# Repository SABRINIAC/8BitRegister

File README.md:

# CPU Registers & Tristate Buffers for the SABRINIAC
This project creates the PCBs for my CPU registers and the tristate buffers to I/O with them.

It is for my '60s inspired computer im making base don the Intel 8080. At the time of writing this I have RAM + it's clock done and the ALU Modules done. After I get the registers + buffers I'll only have to make a motherboard and an opcode decoder/microcode.

The SABRINIAC is my '60s inspired, transistor based,, Intel 8008 Architecture computer. Every part of it from the instruction decoder to the alu will be built using purely transistors.

You can check out the other repos for the SABRINAIC's parts [here](https://github.com/orgs/SABRINIAC/repositories) or you can check out the ALU's repo which explains in more detail what the SABRINIAC is [here](https://github.com/SABRINIAC/ALU-Components)

How to assemble? Just solder on all of the 2N2222 Transistors (or other NPN transitors) and 0603 1kohm resistors

BOM:

| Part Name | Count | Link | Cost |
|-----------|-------|------|------|
| Register PCBs | 18 | From JLCPCB | $10.20 |
| Tri-State Buffer PCBs | 26 | From JLCPCB | $13.30 |
| 2N2222 NPN Transistors | 1406 | https://www.aliexpress.us/item/3256806831821651.html | $15 |
| 0603 SMD 1kohm Resistors | 2684 | https://www.aliexpress.us/item/3256805937811409.html | $12.56 |
| Pin headers | Any combination of 1xN Right Angle Male Pin Headers to make up 1x854 | I already have them but something like this: https://www.aliexpress.us/item/3256803319359683.html | $3 |
| Total | - | - | ~$70 |

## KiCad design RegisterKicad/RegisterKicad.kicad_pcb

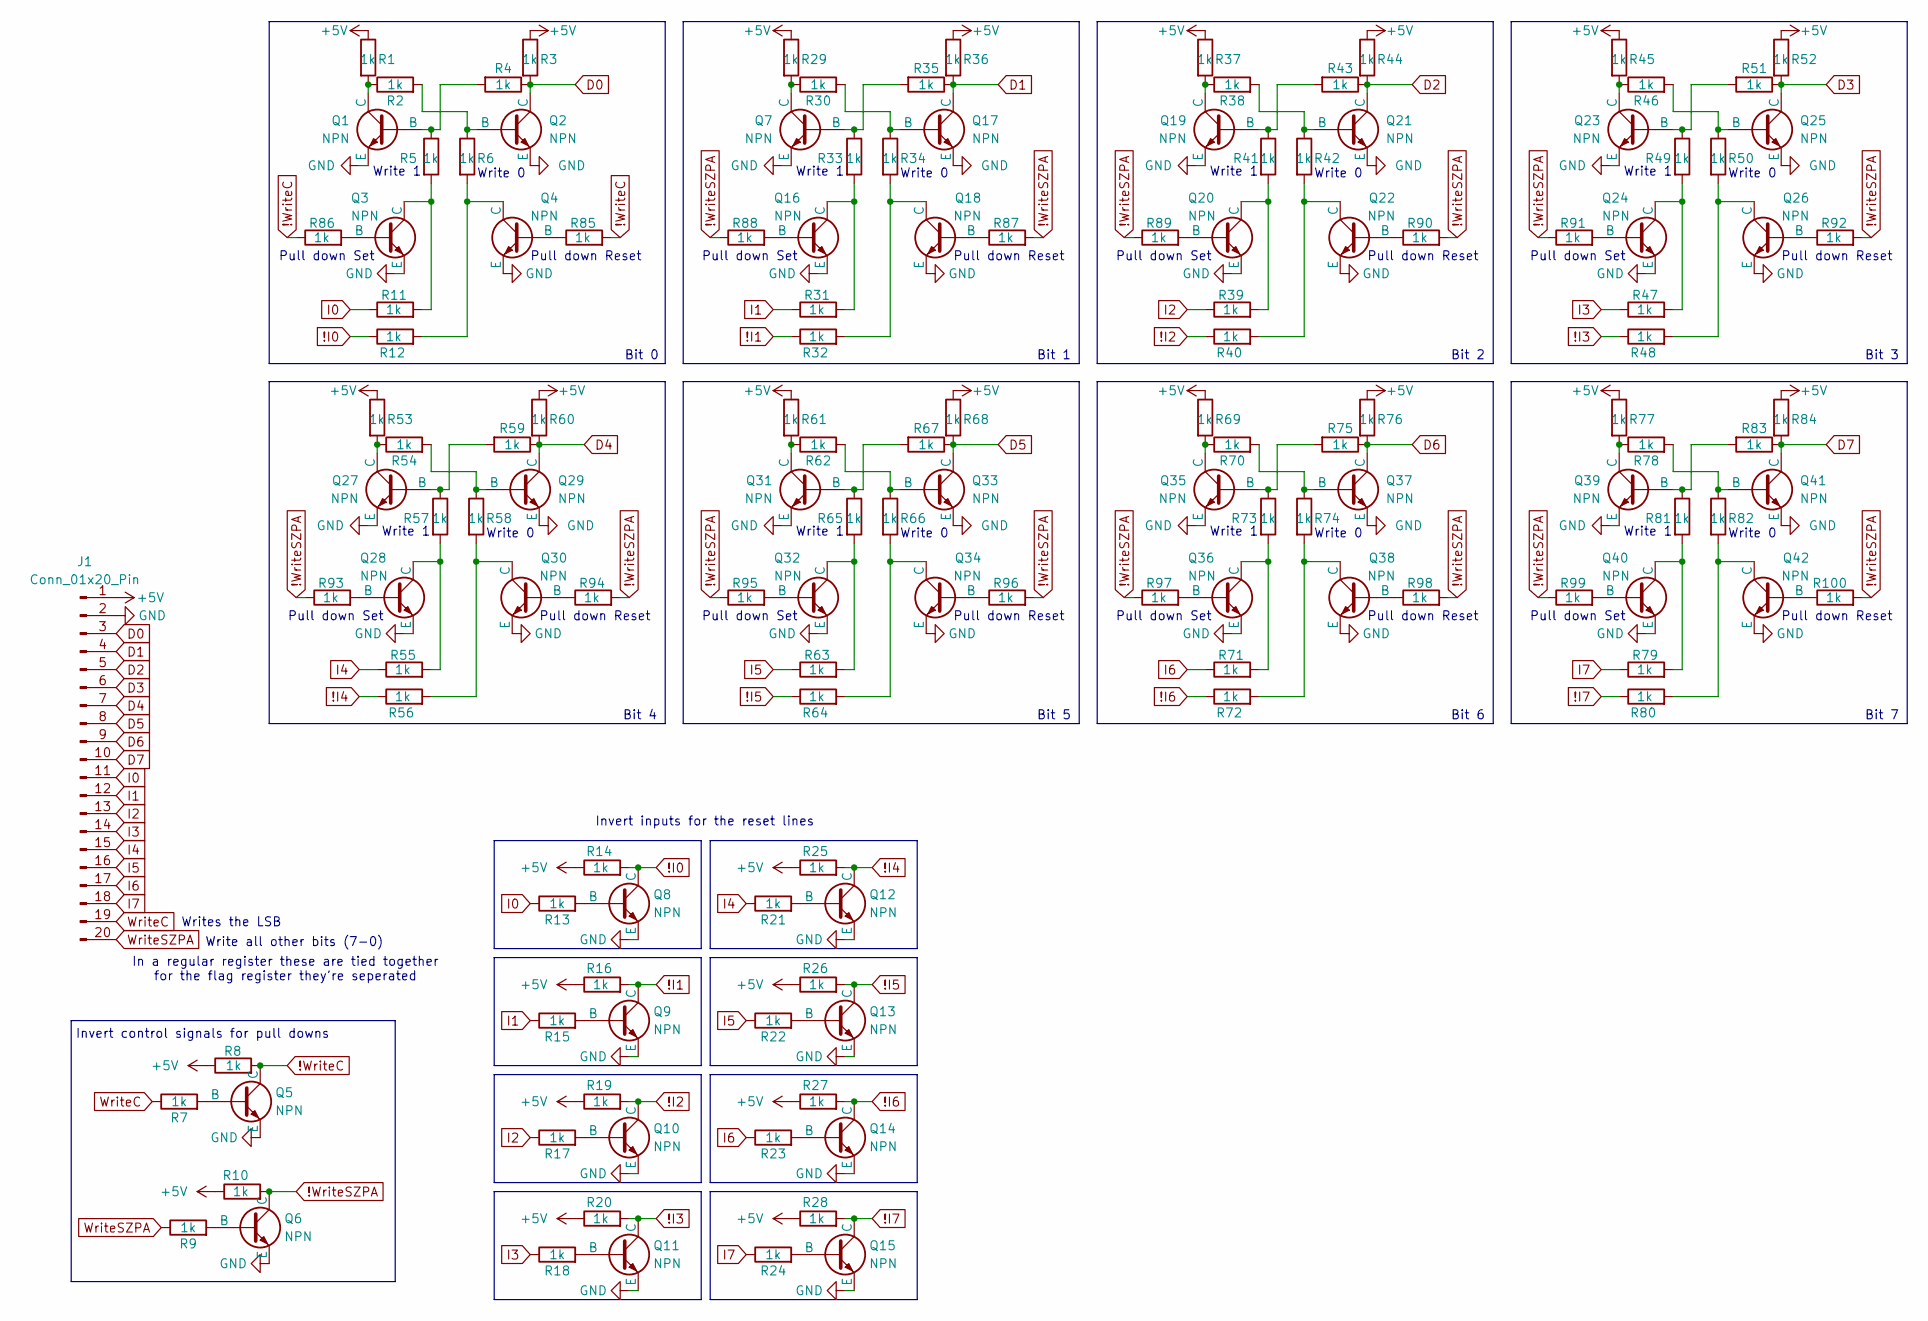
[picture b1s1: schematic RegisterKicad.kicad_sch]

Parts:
J1: Conn_01x20_Pin; PinHeader_1x20_P2.54mm_Horizontal
Q1, Q2, Q3, Q4, Q5, Q6, Q7, Q8, Q9, Q10, Q11, Q12, Q13, Q14, Q15, Q16, Q17, Q18, Q19, Q20, Q21, Q22, Q23, Q24, Q25, Q26, Q27, Q28, Q29, Q30, Q31, Q32, Q33, Q34, Q35, Q36, Q37, Q38, Q39, Q40, Q41, Q42: NPN; TO-92
R1, R2, R3, R4, R5, R6, R7, R8, R9, R10, R11, R12, R13, R14, R15, R16, R17, R18, R19, R20, R21, R22, R23, R24, R25, R26, R27, R28, R29, R30, R31, R32, R33, R34, R35, R36, R37, R38, R39, R40, R41, R42, R43, R44, R45, R46, R47, R48, R49, R50, R51, R52, R53, R54, R55, R56, R57, R58, R59, R60, R61, R62, R63, R64, R65, R66, R67, R68, R69, R70, R71, R72, R73, R74, R75, R76, R77, R78, R79, R80, R81, R82, R83, R84, R85, R86, R87, R88, R89, R90, R91, R92, R93, R94, R95, R96, R97, R98, R99, R100: 1k; R_0603_1608Metric_Pad0.98x0.95mm_HandSolder

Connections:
!I0: Q8.1 (C), R12.1, R14.2
!I1: Q9.1 (C), R16.2, R32.1
!I2: Q10.1 (C), R19.2, R40.1
!I3: Q11.1 (C), R20.2, R48.1
!I4: Q12.1 (C), R25.2, R56.1
!I5: Q13.1 (C), R26.2, R64.1
!I6: Q14.1 (C), R27.2, R72.1
!I7: Q15.1 (C), R28.2, R80.1
!WriteC: Q5.1 (C), R8.2, R85.2, R86.1
!WriteSZPA: Q6.1 (C), R10.2, R87.2, R88.1, R89.1, R90.2, R91.1, R92.2, R93.1, R94.2, R95.1, R96.2, R97.1, R98.2, R99.1, R100.2
+5V: J1.1, R1.1, R3.1, R8.1, R10.1, R14.1, R16.1, R19.1, R20.1, R25.1, R26.1, R27.1, R28.1, R29.1, R36.1, R37.1, R44.1, R45.1, R52.1, R53.1, R60.1, R61.1, R68.1, R69.1, R76.1, R77.1, R84.1
D0: J1.3, Q2.1 (C), R3.2, R4.1
D1: J1.4, Q17.1 (C), R35.1, R36.2
D2: J1.5, Q21.1 (C), R43.1, R44.2
D3: J1.6, Q25.1 (C), R51.1, R52.2
D4: J1.7, Q29.1 (C), R59.1, R60.2
D5: J1.8, Q33.1 (C), R67.1, R68.2
D6: J1.9, Q37.1 (C), R75.1, R76.2
D7: J1.10, Q41.1 (C), R83.1, R84.2
GND: J1.2, Q1.3 (E), Q2.3 (E), Q3.3 (E), Q4.3 (E), Q5.3 (E), Q6.3 (E), Q7.3 (E), Q8.3 (E), Q9.3 (E), Q10.3 (E), Q11.3 (E), Q12.3 (E), Q13.3 (E), Q14.3 (E), Q15.3 (E), Q16.3 (E), Q17.3 (E), Q18.3 (E), Q19.3 (E), Q20.3 (E), Q21.3 (E), Q22.3 (E), Q23.3 (E), Q24.3 (E), Q25.3 (E), Q26.3 (E), Q27.3 (E), Q28.3 (E), Q29.3 (E), Q30.3 (E), Q31.3 (E), Q32.3 (E), Q33.3 (E), Q34.3 (E), Q35.3 (E), Q36.3 (E), Q37.3 (E), Q38.3 (E), Q39.3 (E), Q40.3 (E), Q41.3 (E), Q42.3 (E)
I0: J1.11, R11.1, R13.1
I1: J1.12, R15.1, R31.1
I2: J1.13, R17.1, R39.1
I3: J1.14, R18.1, R47.1
I4: J1.15, R21.1, R55.1
I5: J1.16, R22.1, R63.1
I6: J1.17, R23.1, R71.1
I7: J1.18, R24.1, R79.1
unnamed: Q1.2 (B), R4.2, R5.1
unnamed: Q1.1 (C), R1.2, R2.1
unnamed: Q2.2 (B), R2.2, R6.1
unnamed: Q3.2 (B), R86.2
unnamed: Q3.1 (C), R5.2, R11.2
unnamed: Q4.2 (B), R85.1
unnamed: Q4.1 (C), R6.2, R12.2
unnamed: Q5.2 (B), R7.2
unnamed: Q6.2 (B), R9.2
unnamed: Q7.2 (B), R33.1, R35.2
unnamed: Q7.1 (C), R29.2, R30.1
unnamed: Q8.2 (B), R13.2
unnamed: Q9.2 (B), R15.2
unnamed: Q10.2 (B), R17.2
unnamed: Q11.2 (B), R18.2
unnamed: Q12.2 (B), R21.2
unnamed: Q13.2 (B), R22.2
unnamed: Q14.2 (B), R23.2
unnamed: Q15.2 (B), R24.2
unnamed: Q16.2 (B), R88.2
unnamed: Q16.1 (C), R31.2, R33.2
unnamed: Q17.2 (B), R30.2, R34.1
unnamed: Q18.2 (B), R87.1
unnamed: Q18.1 (C), R32.2, R34.2
unnamed: Q19.2 (B), R41.1, R43.2
unnamed: Q19.1 (C), R37.2, R38.1
unnamed: Q20.2 (B), R89.2
unnamed: Q20.1 (C), R39.2, R41.2
unnamed: Q21.2 (B), R38.2, R42.1
unnamed: Q22.2 (B), R90.1
unnamed: Q22.1 (C), R40.2, R42.2
unnamed: Q23.2 (B), R49.1, R51.2
unnamed: Q23.1 (C), R45.2, R46.1
unnamed: Q24.2 (B), R91.2
unnamed: Q24.1 (C), R47.2, R49.2
unnamed: Q25.2 (B), R46.2, R50.1
unnamed: Q26.2 (B), R92.1
unnamed: Q26.1 (C), R48.2, R50.2
unnamed: Q27.2 (B), R57.1, R59.2
unnamed: Q27.1 (C), R53.2, R54.1
unnamed: Q28.2 (B), R93.2
unnamed: Q28.1 (C), R55.2, R57.2
unnamed: Q29.2 (B), R54.2, R58.1
unnamed: Q30.2 (B), R94.1
unnamed: Q30.1 (C), R56.2, R58.2
unnamed: Q31.2 (B), R65.1, R67.2
unnamed: Q31.1 (C), R61.2, R62.1
unnamed: Q32.2 (B), R95.2
unnamed: Q32.1 (C), R63.2, R65.2
unnamed: Q33.2 (B), R62.2, R66.1
unnamed: Q34.2 (B), R96.1
unnamed: Q34.1 (C), R64.2, R66.2
unnamed: Q35.2 (B), R73.1, R75.2
unnamed: Q35.1 (C), R69.2, R70.1
unnamed: Q36.2 (B), R97.2
unnamed: Q36.1 (C), R71.2, R73.2
unnamed: Q37.2 (B), R70.2, R74.1
unnamed: Q38.2 (B), R98.1
unnamed: Q38.1 (C), R72.2, R74.2
unnamed: Q39.2 (B), R81.1, R83.2
unnamed: Q39.1 (C), R77.2, R78.1
unnamed: Q40.2 (B), R99.2
unnamed: Q40.1 (C), R79.2, R81.2
unnamed: Q41.2 (B), R78.2, R82.1
unnamed: Q42.2 (B), R100.1
unnamed: Q42.1 (C), R80.2, R82.2
WriteC: J1.19, R7.1
WriteSZPA: J1.20, R9.1

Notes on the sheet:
Bit 2
In a regular register these are tied together for the flag register they're seperated
Pull down Reset
Write 1
Bit 1
Pull down Set
Invert control signals for pull downs
Write 0
Invert inputs for the reset lines
Bit 6
Bit 3
Bit 5
Bit 7
Bit 4
Bit 0
Write all other bits (7-0)
Writes the LSB

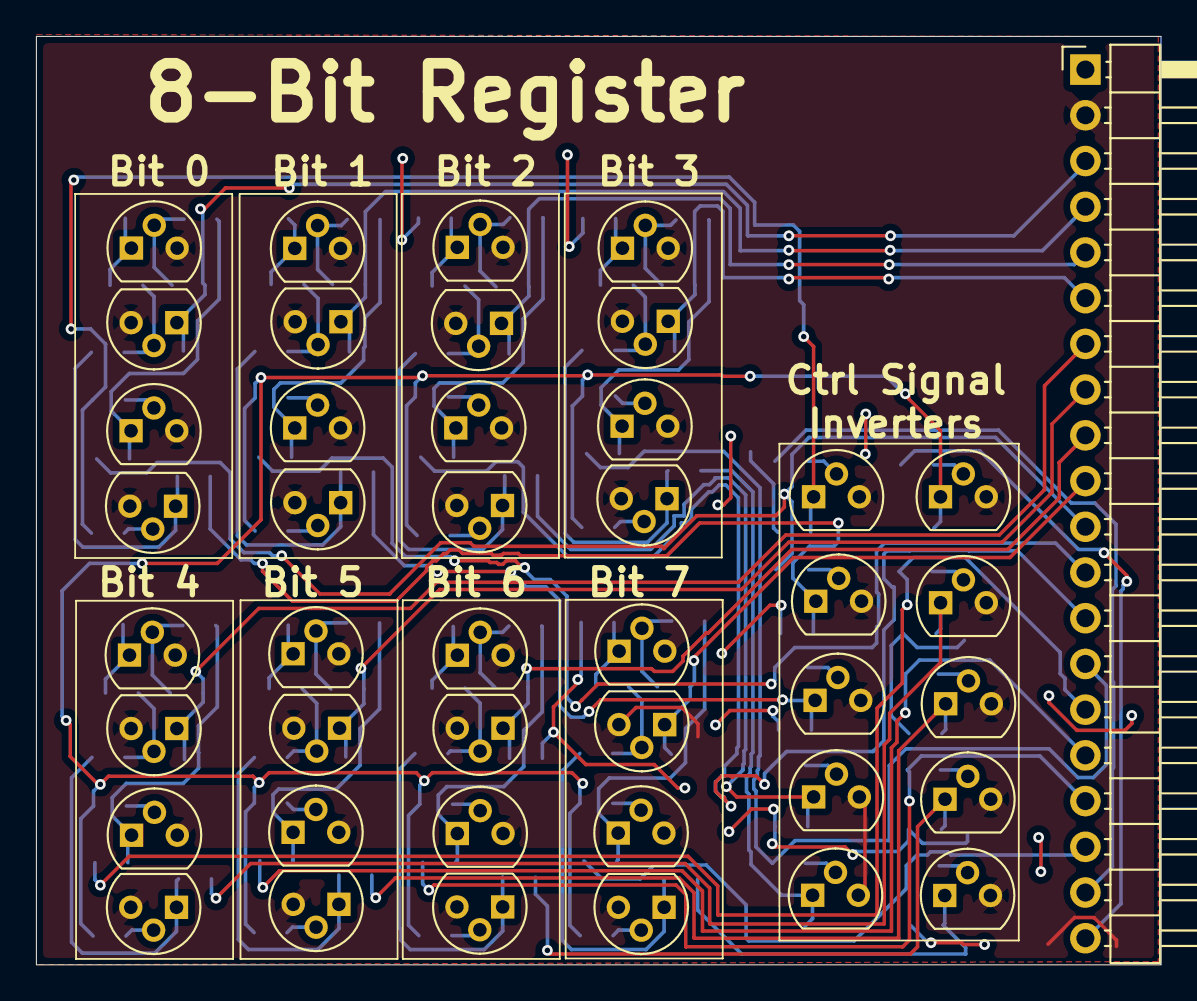
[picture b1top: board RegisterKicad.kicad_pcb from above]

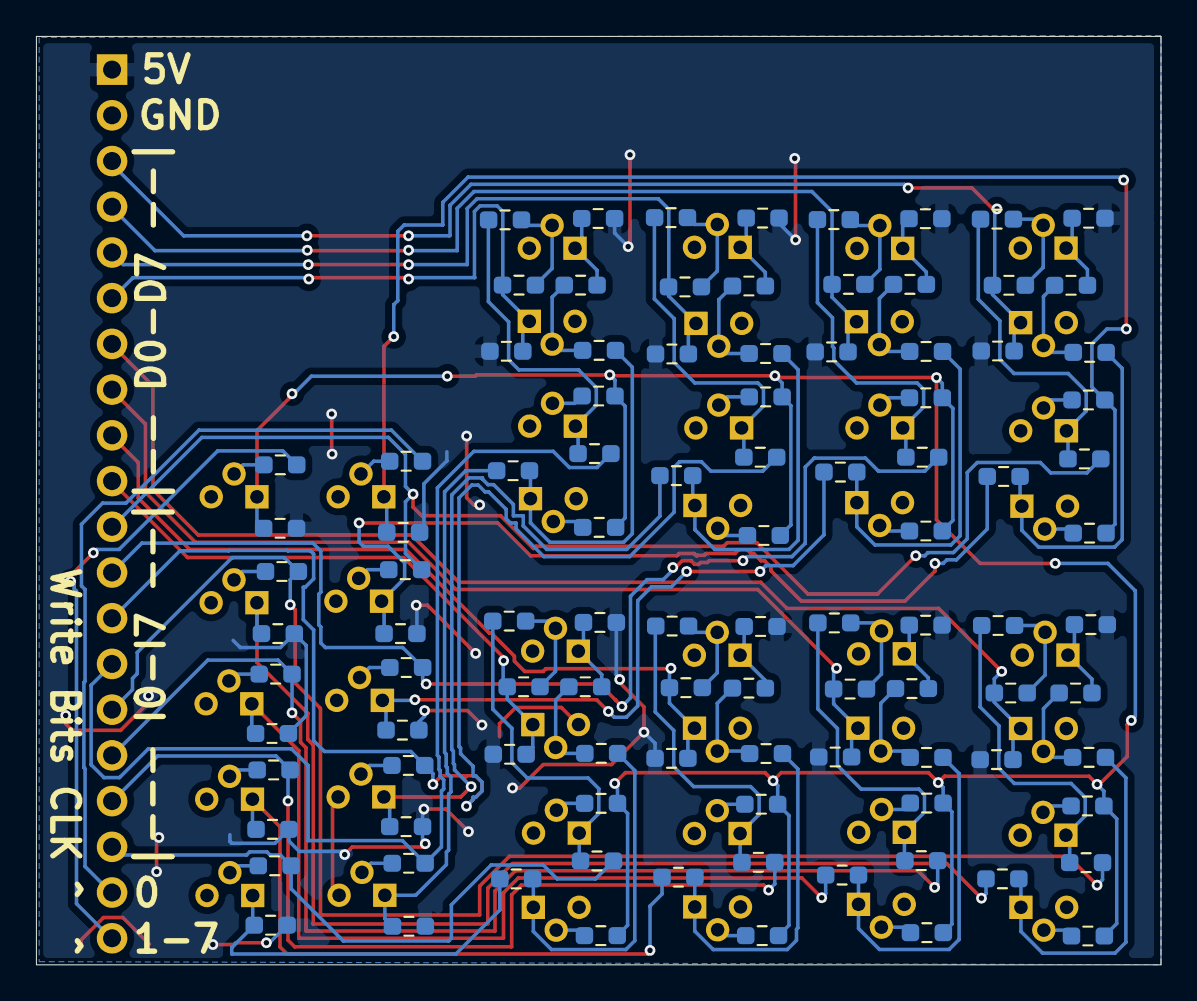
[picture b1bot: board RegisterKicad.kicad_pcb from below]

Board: 2 copper layers, 62.5 x 51.6 mm, 143 parts (100 on the bottom side), 96 nets.

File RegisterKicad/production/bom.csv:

Designator,Footprint,Quantity,Value,LCSC Part #
J1,PinHeader_1x20_P2.54mm_Horizontal,1,Conn_01x20_Pin,
"Q1, Q10, Q11, Q12, Q13, Q14, Q15, Q16, Q17, Q18, Q19, Q2, Q20, Q21, Q22, Q23, Q24, Q25, Q26, Q27, Q28, Q29, Q3, Q30, Q31, Q32, Q33, Q34, Q35, Q36, Q37, Q38, Q39, Q4, Q40, Q41, Q42, Q5, Q6, Q7, Q8, Q9",TO-92,42,NPN,
"R1, R10, R100, R11, R12, R13, R14, R15, R16, R17, R18, R19, R2, R20, R21, R22, R23, R24, R25, R26, R27, R28, R29, R3, R30, R31, R32, R33, R34, R35, R36, R37, R38, R39, R4, R40, R41, R42, R43, R44, R45, R46, R47, R48, R49, R5, R50, R51, R52, R53, R54, R55, R56, R57, R58, R59, R6, R60, R61, R62, R63, R64, R65, R66, R67, R68, R69, R7, R70, R71, R72, R73, R74, R75, R76, R77, R78, R79, R8, R80, R81, R82, R83, R84, R85, R86, R87, R88, R89, R9, R90, R91, R92, R93, R94, R95, R96, R97, R98, R99",0603,100,1k,

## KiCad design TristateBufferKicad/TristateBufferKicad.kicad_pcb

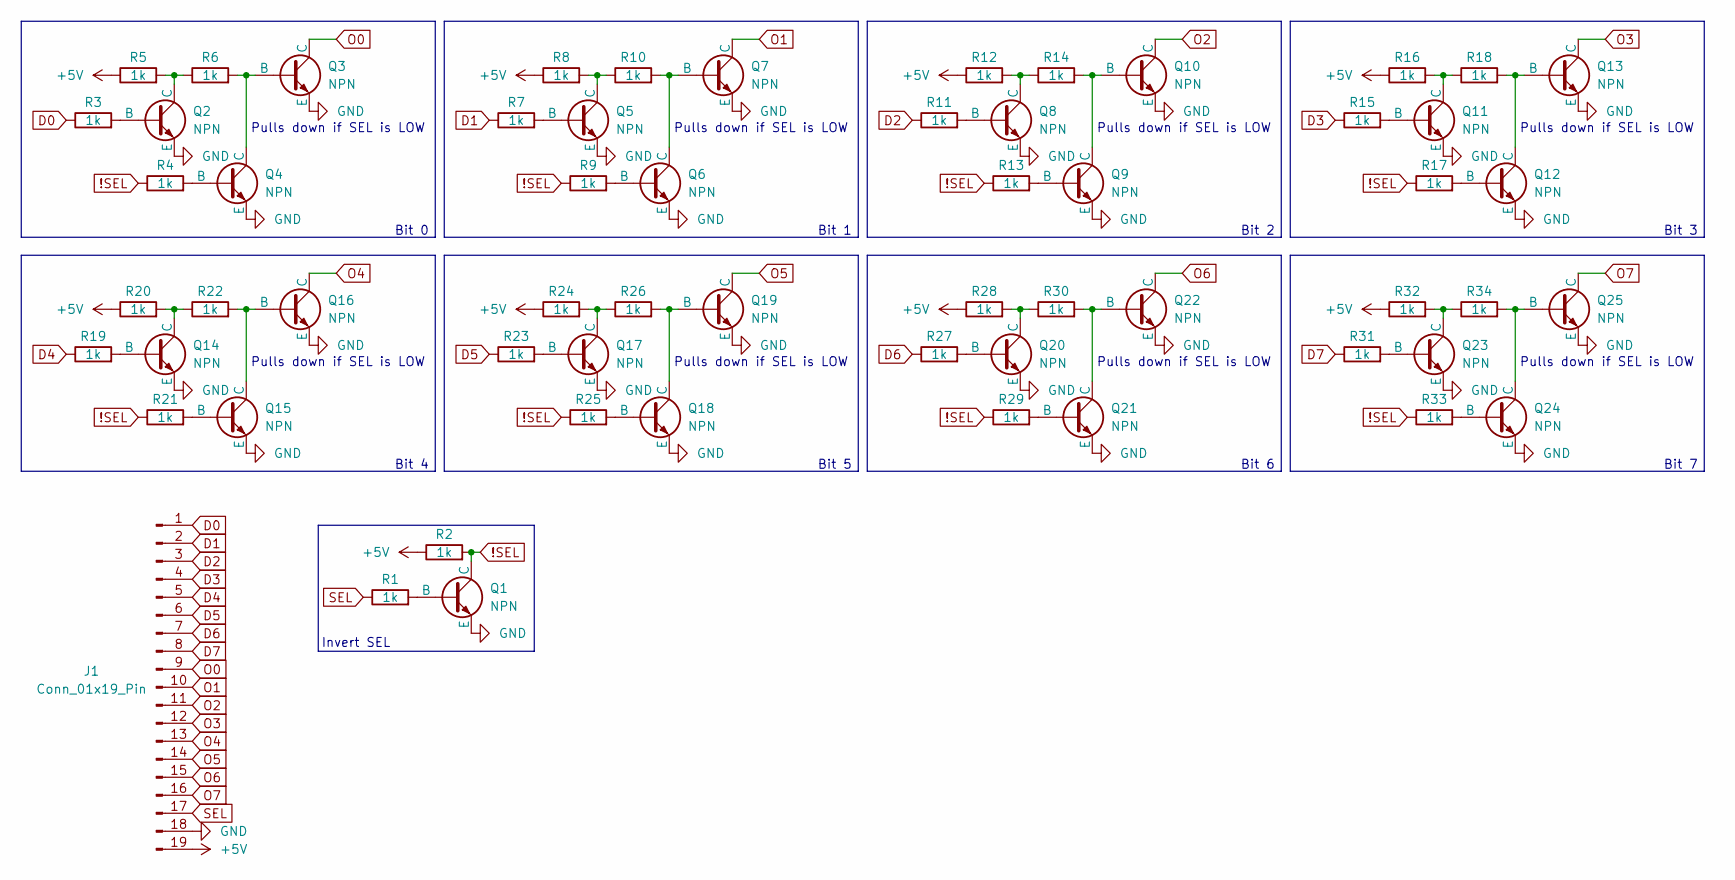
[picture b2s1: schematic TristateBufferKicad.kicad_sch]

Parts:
J1: Conn_01x19_Pin; PinHeader_1x19_P2.54mm_Horizontal
Q1, Q2, Q3, Q4, Q5, Q6, Q7, Q8, Q9, Q10, Q11, Q12, Q13, Q14, Q15, Q16, Q17, Q18, Q19, Q20, Q21, Q22, Q23, Q24, Q25: NPN; TO-92
R1, R2, R3, R4, R5, R6, R7, R8, R9, R10, R11, R12, R13, R14, R15, R16, R17, R18, R19, R20, R21, R22, R23, R24, R25, R26, R27, R28, R29, R30, R31, R32, R33, R34: 1k; R_0603_1608Metric_Pad0.98x0.95mm_HandSolder

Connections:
!SEL: Q1.1 (C), R2.2, R4.1, R9.1, R13.1, R17.1, R21.1, R25.1, R29.1, R33.1
+5V: J1.19, R2.1, R5.1, R8.1, R12.1, R16.1, R20.1, R24.1, R28.1, R32.1
D0: J1.1, R3.1
D1: J1.2, R7.1
D2: J1.3, R11.1
D3: J1.4, R15.1
D4: J1.5, R19.1
D5: J1.6, R23.1
D6: J1.7, R27.1
D7: J1.8, R31.1
GND: J1.18, Q1.3 (E), Q2.3 (E), Q3.3 (E), Q4.3 (E), Q5.3 (E), Q6.3 (E), Q7.3 (E), Q8.3 (E), Q9.3 (E), Q10.3 (E), Q11.3 (E), Q12.3 (E), Q13.3 (E), Q14.3 (E), Q15.3 (E), Q16.3 (E), Q17.3 (E), Q18.3 (E), Q19.3 (E), Q20.3 (E), Q21.3 (E), Q22.3 (E), Q23.3 (E), Q24.3 (E), Q25.3 (E)
unnamed: Q1.2 (B), R1.2
unnamed: Q2.2 (B), R3.2
unnamed: Q2.1 (C), R5.2, R6.1
unnamed: Q3.2 (B), Q4.1 (C), R6.2
unnamed: Q4.2 (B), R4.2
unnamed: Q5.2 (B), R7.2
unnamed: Q5.1 (C), R8.2, R10.1
unnamed: Q6.2 (B), R9.2
unnamed: Q6.1 (C), Q7.2 (B), R10.2
unnamed: Q8.2 (B), R11.2
unnamed: Q8.1 (C), R12.2, R14.1
unnamed: Q9.2 (B), R13.2
unnamed: Q9.1 (C), Q10.2 (B), R14.2
unnamed: Q11.2 (B), R15.2
unnamed: Q11.1 (C), R16.2, R18.1
unnamed: Q12.2 (B), R17.2
unnamed: Q12.1 (C), Q13.2 (B), R18.2
unnamed: Q14.2 (B), R19.2
unnamed: Q14.1 (C), R20.2, R22.1
unnamed: Q15.2 (B), R21.2
unnamed: Q15.1 (C), Q16.2 (B), R22.2
unnamed: Q17.2 (B), R23.2
unnamed: Q17.1 (C), R24.2, R26.1
unnamed: Q18.2 (B), R25.2
unnamed: Q18.1 (C), Q19.2 (B), R26.2
unnamed: Q20.2 (B), R27.2
unnamed: Q20.1 (C), R28.2, R30.1
unnamed: Q21.2 (B), R29.2
unnamed: Q21.1 (C), Q22.2 (B), R30.2
unnamed: Q23.2 (B), R31.2
unnamed: Q23.1 (C), R32.2, R34.1
unnamed: Q24.2 (B), R33.2
unnamed: Q24.1 (C), Q25.2 (B), R34.2
O0: J1.9, Q3.1 (C)
O1: J1.10, Q7.1 (C)
O2: J1.11, Q10.1 (C)
O3: J1.12, Q13.1 (C)
O4: J1.13, Q16.1 (C)
O5: J1.14, Q19.1 (C)
O6: J1.15, Q22.1 (C)
O7: J1.16, Q25.1 (C)
SEL: J1.17, R1.1

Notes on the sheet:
Bit 2
Pulls down if SEL is LOW
Bit 1
Invert SEL
Bit 0
Bit 5
Bit 3
Bit 6
Bit 7
Bit 4

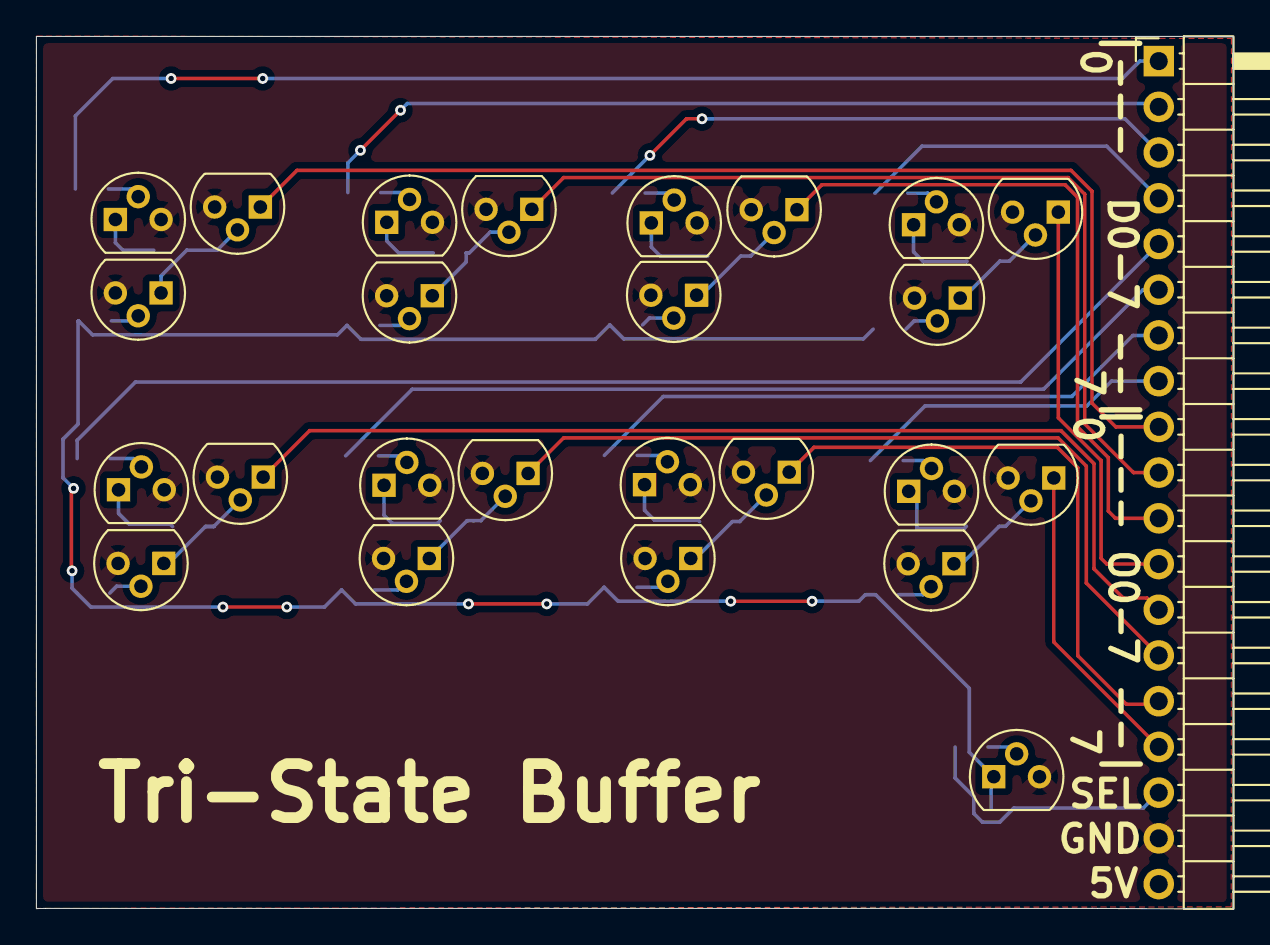
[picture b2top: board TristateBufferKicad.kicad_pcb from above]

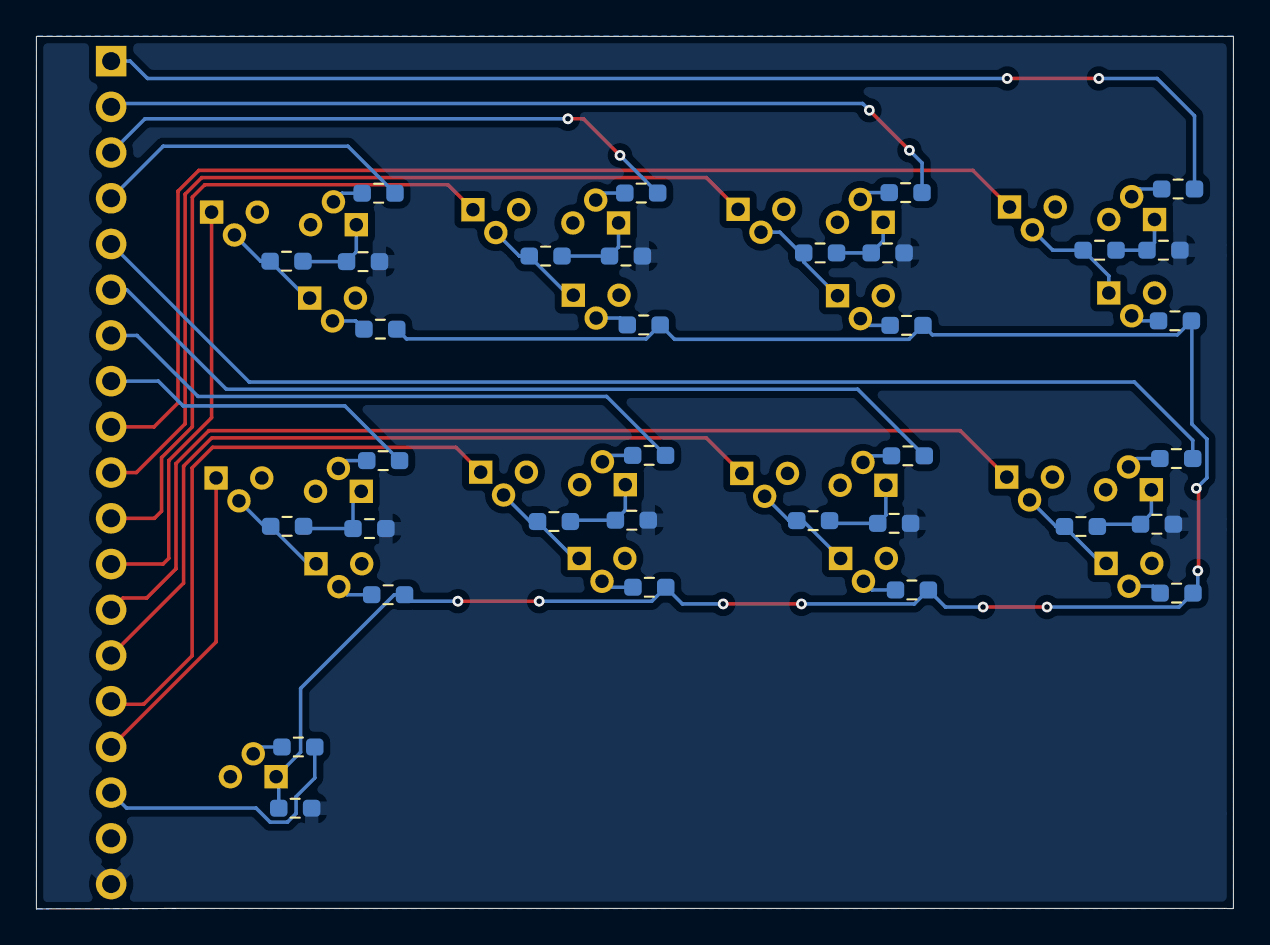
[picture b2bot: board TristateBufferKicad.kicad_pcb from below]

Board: 2 copper layers, 66.5 x 48.5 mm, 60 parts (34 on the bottom side), 53 nets.

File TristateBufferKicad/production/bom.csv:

Designator,Footprint,Quantity,Value,LCSC Part #
J1,PinHeader_1x19_P2.54mm_Horizontal,1,Conn_01x19_Pin,
"Q1, Q10, Q11, Q12, Q13, Q14, Q15, Q16, Q17, Q18, Q19, Q2, Q20, Q21, Q22, Q23, Q24, Q25, Q3, Q4, Q5, Q6, Q7, Q8, Q9",TO-92,25,NPN,
"R1, R10, R11, R12, R13, R14, R15, R16, R17, R18, R19, R2, R20, R21, R22, R23, R24, R25, R26, R27, R28, R29, R3, R30, R31, R32, R33, R34, R4, R5, R6, R7, R8, R9",0603,34,1k,
